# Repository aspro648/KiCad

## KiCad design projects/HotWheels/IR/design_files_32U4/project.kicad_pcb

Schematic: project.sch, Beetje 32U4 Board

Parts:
C1: 0.1uF; C_0805
C2: 1uF; C_0603
C3: 10uF; C_0805
CON1: ISP; Pin_Header_Straight_2x03_Pitch2.54mm
D5, D6: LED; LED_D3.0mm
D7, D8: IR; LED_D3.0mm
F1: Polyfuse; R_1206
J1: I2C; Molex_PicoBlade_53048-0410_04x1.25mm_Angled
J2: RJ45; RJ45_8
J3: SERVO_1; Pin_Header_Angled_1x03_Pitch2.54mm
J4: SERVO; Pin_Header_Angled_1x03_Pitch2.54mm
Q1, Q2: Q_Photo_NPN; PHOTOTRANS
R1, R2, R3, R8: JMP; Jumper
R4, R5: 4K7; R_0603
R6, R7: 22; R_0603
R9, R12: 10K; R_0603
R10, R11: 100; R_0603
R13, R14: 330; R_0603
SW1: D4; SW_PUSH_6mm
U1: ATMEGA32U4-AU; TQFP-44_10x10mm_Pitch0.8mm
X1: USB; USB_Micro-B_Molex-105017-0001
Y1: 8 Mhz; Resonator_SMD_CTSC_1.3mmx3.2mm

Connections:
/A0: U1.36 ((ADC7/TDI)PF7)
/A1: U1.37 ((ADC6/TDO)PF6)
/A2: U1.38 ((ADC5/TMS)PF5)
/A3: U1.39 ((ADC4/TCK)PF4)
/A4: U1.40 ((ADC1)PF1)
/A5: U1.41 ((ADC0)PF0)
/AREF: U1.42 (AREF)
/D0: U1.20 ((RXD/INT2)PD2)
/D1: U1.21 ((TXD/INT3)PD3)
/D5: R2.1, R13.2, U1.31 ((OC3A/~OC4A~)PC6)
/D6: J2.5, R2.2, U1.27 ((T0/OC4D/ADC10)PD7)
/D7: U1.1 ((INT6/AIN0)PE6)
/D8: Q1.1 (C), R1.1, R9.1, U1.28 ((ADC11/PCINT4)PB4)
/D9: R3.1, R14.2, U1.29 ((ADC12/OC1A/~OC4B~/PCINT12)PB5)
/D10: SW1.2, U1.30 ((ADC13/OC1B/OC4B/PCINT13)PB6)
/D11: Q2.1 (C), R8.1, R12.1, U1.12 ((OC0A/OC1C/~RTS~/PCINT7)PB7)
/D12: J4.3, U1.26 ((T1/~OC4D~/ADC9)PD6)
/D13: J3.3, U1.32 ((ICP3/CLK0/OC4A)PC7)
/D+: R6.1, U1.4 (D+)
/D-: R7.1, U1.3 (D-)
/MISO: CON1.1, J2.4, R8.2, U1.11 ((PDO/MISO/PCINT3)PB3)
/MOSI: CON1.4, J2.3, R1.2, U1.10 ((PDI/MOSI/PCINT2)PB2)
/SCK: CON1.3, J2.2, R3.2, U1.9 ((SCLK/PCINT1)PB1)
/SCL: J1.4, J2.6, R4.1, U1.18 ((OC0B/SCL/INT0)PD0)
/SDA: J1.3, J2.7, R5.1, U1.19 ((SDA/INT1)PD1)
/~RESET: CON1.5, U1.13 (~RESET~)
GND: C1.2, C2.2, C3.2, CON1.6, D5.1 (K), D6.1 (K), D7.1 (K), D8.1 (K), J1.2, J2.8, J2.9 (SHIELD), J3.2, J4.2, Q1.2 (E), Q2.2 (E), SW1.1, U1.5 (UGND), U1.15 (GND), U1.23 (GND), U1.35 (GND), U1.43 (GND), X1.5 (GND), X1.6 (Shield), Y1.2
unnamed: D5.2 (A), R13.1
unnamed: D6.2 (A), R14.1
unnamed: D7.2 (A), R11.1
unnamed: D8.2 (A), R10.1
unnamed: F1.2, X1.1 (VBUS)
unnamed: R6.2, X1.3 (D+)
unnamed: R7.2, X1.2 (D-)
unnamed: U1.16 (XTAL2), Y1.3
unnamed: U1.17 (XTAL1), Y1.1
VCC: C1.1, C2.1, C3.1, CON1.2, F1.1, J1.1, J2.1, J3.1, J4.1, R4.2, R5.2, R9.2, R10.2, R11.2, R12.2, U1.6 (UCAP), U1.7 (VBUS), U1.14 (VCC), U1.24 (AVCC), U1.33 ((~HWB~)PE2), U1.34 (VCC), U1.44 (AVCC)

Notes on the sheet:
SparkFun's Qwiic: Black = GND Red = 3.3V Blue = SDA Yellow = SCL

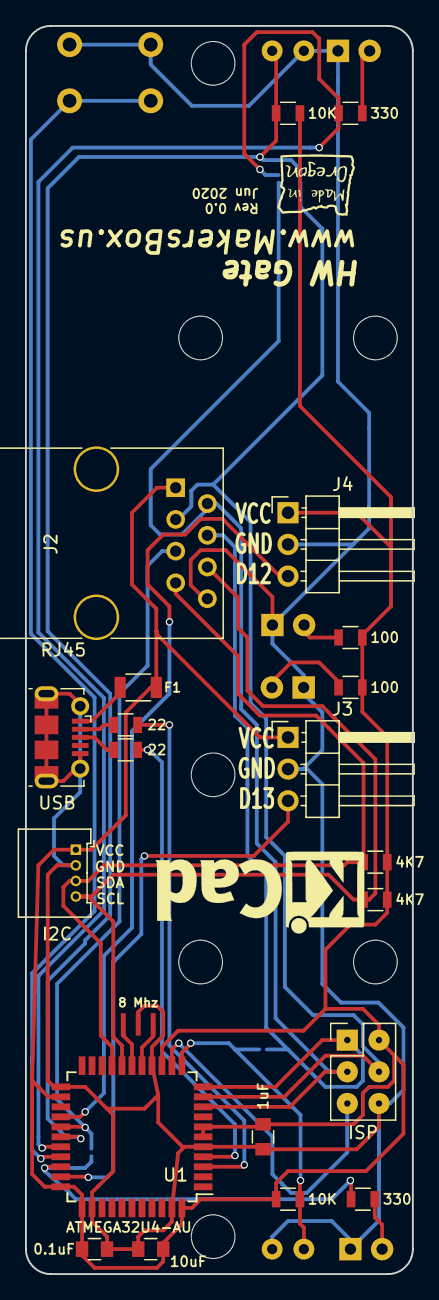
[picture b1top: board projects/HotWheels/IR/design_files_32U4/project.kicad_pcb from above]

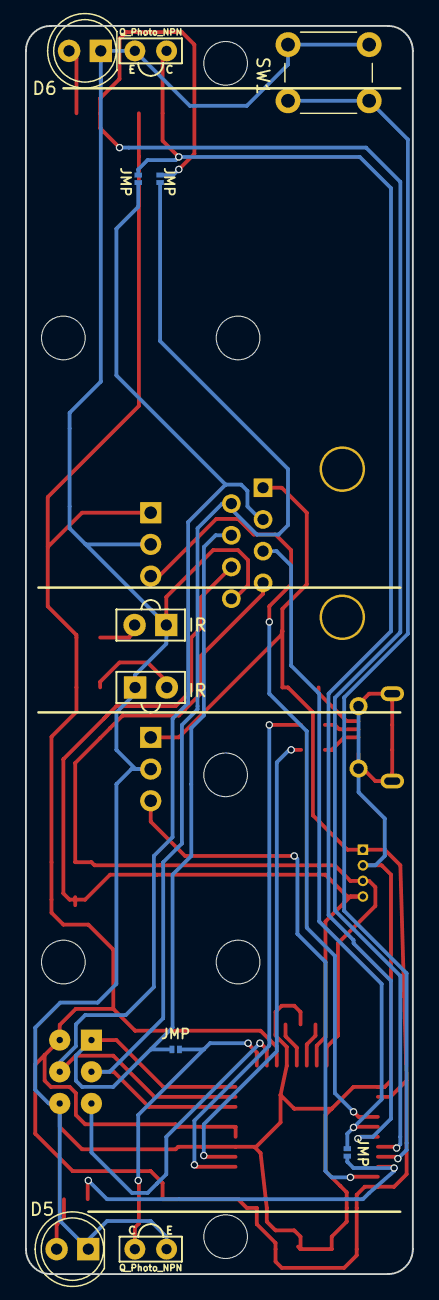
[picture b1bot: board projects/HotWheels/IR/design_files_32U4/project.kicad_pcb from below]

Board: 2 copper layers, 31.0 x 100.0 mm, 34 parts (12 on the bottom side), 27 nets.

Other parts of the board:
VAL: MadeInOregonRev25

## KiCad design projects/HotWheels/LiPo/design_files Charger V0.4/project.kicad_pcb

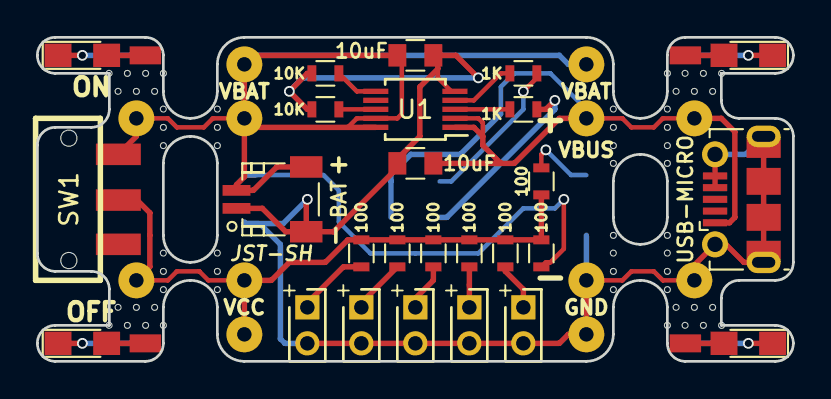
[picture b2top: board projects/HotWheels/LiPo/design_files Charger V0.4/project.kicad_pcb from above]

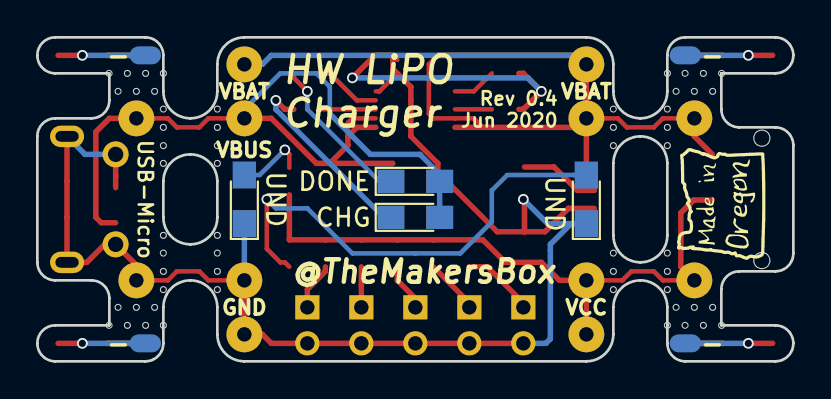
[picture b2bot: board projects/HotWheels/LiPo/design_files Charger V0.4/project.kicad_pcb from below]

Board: 2 copper layers, 42.0 x 18.0 mm, 47 parts (4 on the bottom side), 25 nets.

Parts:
C1, C2: 10uF; C_0805
D2: CHG; LED_0805_HandSoldering
D3: DONE; LED_0805_HandSoldering
D4, D5: UND; LED_0805_HandSoldering
D20, D21, D22, D23: LED; LED_0805_HandSoldering
J1, J6, J7, J8, J9: LED; PIN_HEADER_LED
J2: USB-MICRO; USB_Micro-B_Molex-105017-0001
J3: BAT; JST_SH_SM02B-SRSS-TB_02x1.00mm_Angled
J20, J21, J22, J23: LED; LED_PADS
J44, J45, J46, J47, J48, J49, J54, J55, J56, J57, J58, J59: Conn; SolderWirePad_single_0-8mmDrill
R2, R3: 1K; R_0603
R4, R5: 10K; R_0603
R6, R7, R8, R9, R10, R11, R12: 100; R_0603
SW1: SW_SPDT; SPST_SMD
U1: MCP73833; MSOP-10_3x3mm_Pitch0.5mm
VAL: MadeInOregonRev25

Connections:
/VBAT: C2.1, J3.2, J44.1, J54.1, J56.1, J58.1, SW1.1, U1.9, U1.10
GND: C1.2, C2.2, D4.1, D5.1, J1.2, J2.4, J2.5, J3.1, J6.2, J7.2, J8.2, J9.2, J45.1, J47.1, J49.1, R4.2, R5.2, U1.5
unnamed: D2.1, R2.2
unnamed: D3.1, R3.2
unnamed: D4.2, R11.2
unnamed: D5.2, R12.2
unnamed: D20.1, J20.2
unnamed: D20.2, J20.1
unnamed: D21.1, J21.2
unnamed: D21.2, J21.1
unnamed: D22.1, J22.2
unnamed: D22.2, J22.1
unnamed: D23.1, J23.2
unnamed: D23.2, J23.1
unnamed: J1.1, R6.2
unnamed: J6.1, R7.2
unnamed: J7.1, R8.2
unnamed: J8.1, R9.2
unnamed: J9.1, R10.2
unnamed: R2.1, U1.3
unnamed: R3.1, U1.4
unnamed: R4.1, U1.8
unnamed: R5.1, U1.6
VBUS: C1.1, D2.2, D3.2, J2.1, J46.1, J48.1, U1.1, U1.2
VCC: J55.1, J57.1, J59.1, R6.1, R7.1, R8.1, R9.1, R10.1, R11.1, R12.1, SW1.2

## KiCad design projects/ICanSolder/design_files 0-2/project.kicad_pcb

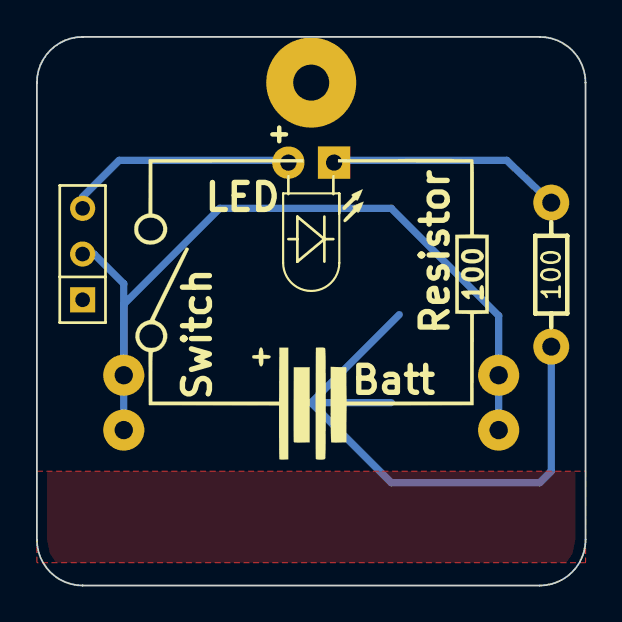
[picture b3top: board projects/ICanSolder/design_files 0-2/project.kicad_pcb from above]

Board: 2 copper layers, 30.5 x 30.5 mm, 6 parts (1 on the bottom side), 4 nets.

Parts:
BT1: Battery; BATT_CR2032
D1: LED; LED_D3.0mm_Horizontal_O1.27mm_Z2.0mm
R1: 100; Resistor_Horz
SW1: SPDT; SW_Micro_SPST
VAL: MadeInOregonRev25
VAL#2: MB225rev

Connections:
unnamed: BT1.1, SW1.2
unnamed: BT1.2, R1.2
unnamed: D1.1, R1.1
unnamed: D1.2, SW1.3
